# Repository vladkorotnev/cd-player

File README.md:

# ESPer CDP

## Index

* [Firmware](firm)
* [Schematics](sch)
* [Test CD](test-suite)
* [Hoard of Docs](reference)

Read the rest of the readme in the Firmware folder above...

## Rough BOM

* ESPer-CDP dev PCB for IDE bus
* ESP32-WROVER, REV3 or newer with 8MB QIO Flash and 4MB QIO PSRAM
* PCA9555D ×2
* Wolfson WM8805 (sorry, out of production, but you can still buy them here and there)
* PCM5102
* Various resistors and capacitors -- see schematic
* 12MHz XTAL
* IR Receiver and PS2 DVD remote
* ESPer-CDP Keypad PCB
* 8 12x12mm buttons
* Futaba GP1232A02 VFD display

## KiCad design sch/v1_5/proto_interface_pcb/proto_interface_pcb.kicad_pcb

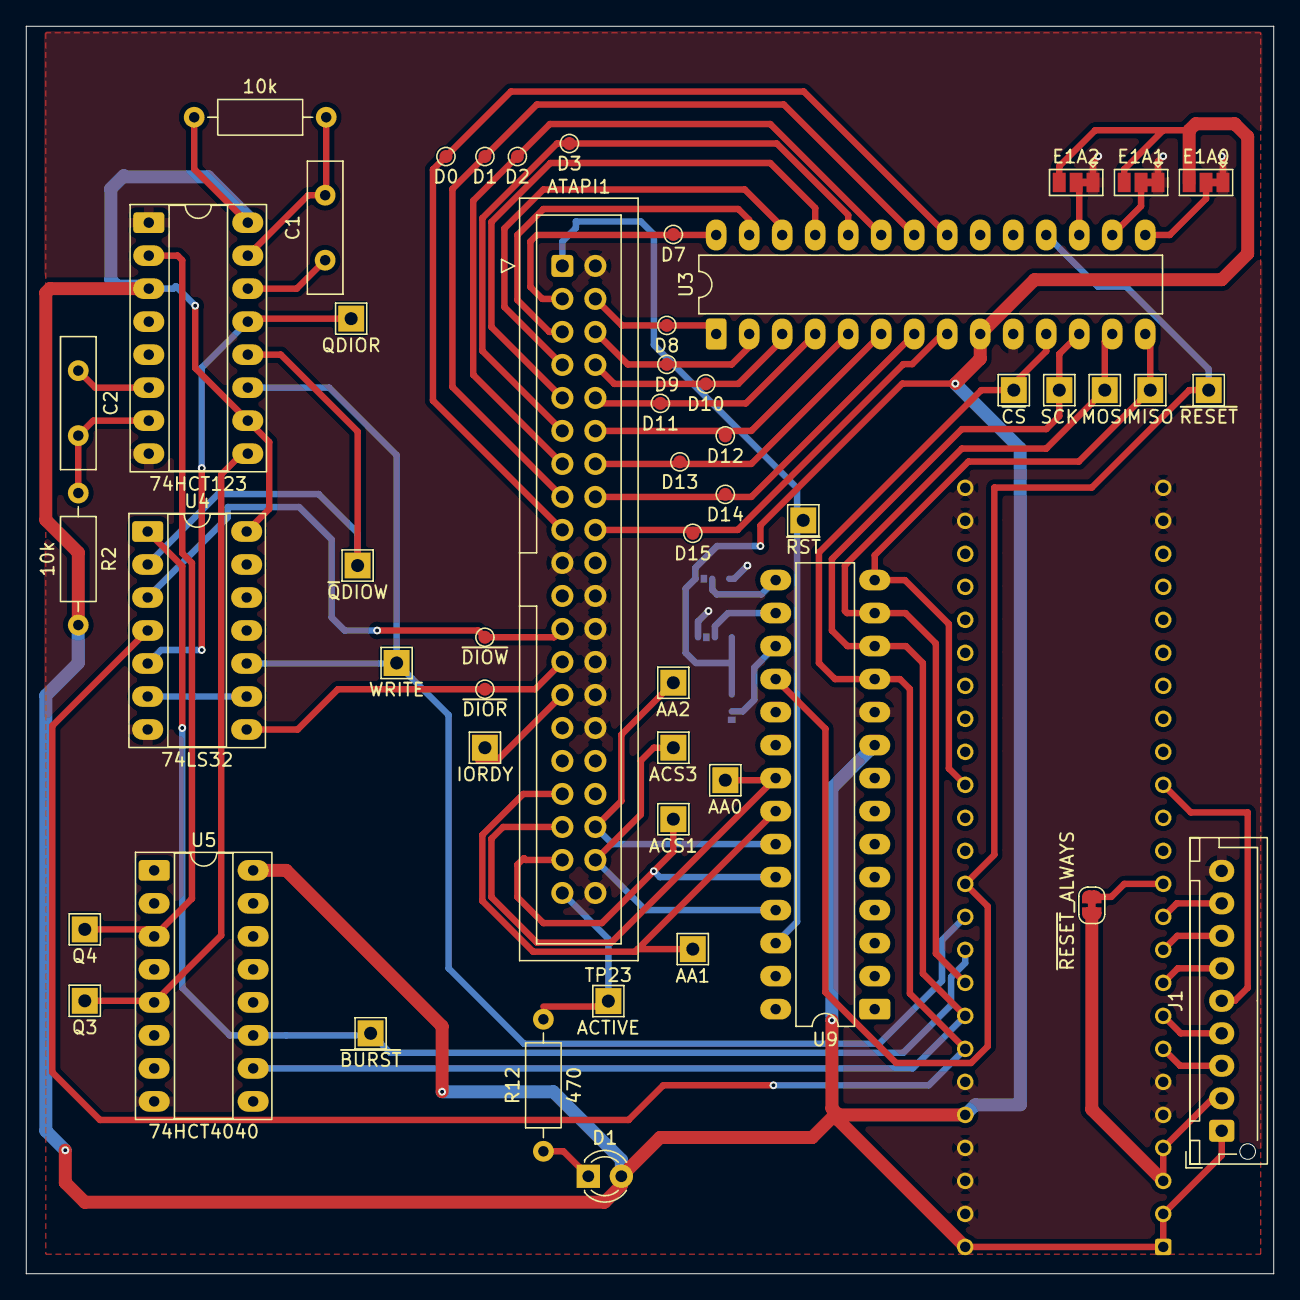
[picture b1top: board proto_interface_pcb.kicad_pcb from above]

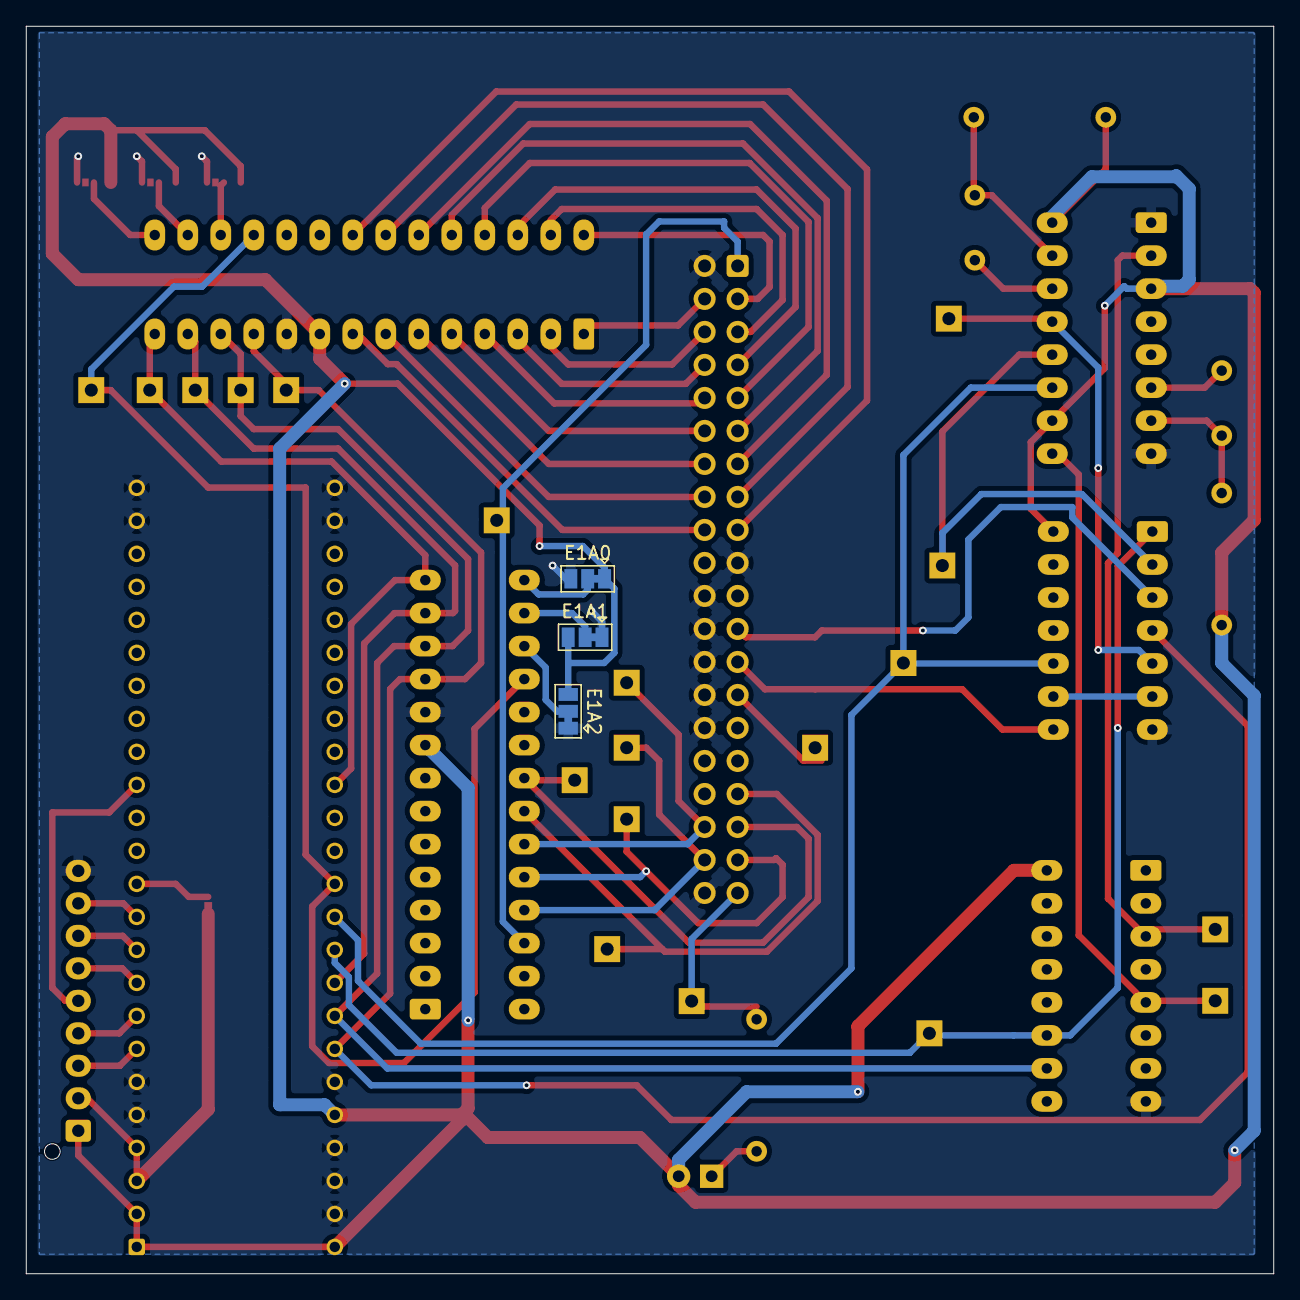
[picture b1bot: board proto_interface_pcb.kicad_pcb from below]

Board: 2 copper layers, 96.0 x 96.0 mm, 55 parts (3 on the bottom side), 59 nets.

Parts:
ATAPI1: IDC-Header_2x20_P2.54mm_Vertical
C1, C2: 220pF; C_Disc_D10.0mm_W2.5mm_P5.00mm
D1: ACTLED; LED_D3.0mm_Clear
J1: Conn_01x09_Socket; JST_XH_B9B-XH-AM_1x09_P2.50mm_Vertical
JP1, JP4: E1A0; SolderJumper-3_P1.3mm_Bridged12_Pad1.0x1.5mm
JP2, JP5: E1A1; SolderJumper-3_P1.3mm_Bridged12_Pad1.0x1.5mm
JP3, JP6: E1A2; SolderJumper-3_P1.3mm_Bridged12_Pad1.0x1.5mm
JP7: ~{RESET}_ALWAYS; SolderJumper-2_P1.3mm_Bridged_RoundedPad1.0x1.5mm
R1, R2: 10k; R_Axial_DIN0207_L6.3mm_D2.5mm_P10.16mm_Horizontal
R12: 470; R_Axial_DIN0207_L6.3mm_D2.5mm_P10.16mm_Horizontal
TP1: D0; TestPoint_Pad_D1.0mm
TP2: D1; TestPoint_Pad_D1.0mm
TP3: D2; TestPoint_Pad_D1.0mm
TP4: D3; TestPoint_Pad_D1.0mm
TP8: D7; TestPoint_Pad_D1.0mm
TP9: D8; TestPoint_Pad_D1.0mm
TP10: D9; TestPoint_Pad_D1.0mm
TP11: D10; TestPoint_Pad_D1.0mm
TP12: D11; TestPoint_Pad_D1.0mm
TP13: D12; TestPoint_Pad_D1.0mm
TP14: D13; TestPoint_Pad_D1.0mm
TP15: D14; TestPoint_Pad_D1.0mm
TP16: D15; TestPoint_Pad_D1.0mm
TP17: IORDY; TestPoint_THTPad_2.0x2.0mm_Drill1.0mm
TP18: AA0; TestPoint_THTPad_2.0x2.0mm_Drill1.0mm
TP19: AA1; TestPoint_THTPad_2.0x2.0mm_Drill1.0mm
TP20: AA2; TestPoint_THTPad_2.0x2.0mm_Drill1.0mm
TP21: ACS1; TestPoint_THTPad_2.0x2.0mm_Drill1.0mm
TP22: ACS3; TestPoint_THTPad_2.0x2.0mm_Drill1.0mm
TP23: ACTIVE; TestPoint_THTPad_2.0x2.0mm_Drill1.0mm
TP24: ~{RST}; TestPoint_THTPad_2.0x2.0mm_Drill1.0mm
TP25: ~{DIOW}; TestPoint_Pad_D1.0mm
TP26: ~{DIOR}; TestPoint_Pad_D1.0mm
TP27: ~{CS}; TestPoint_THTPad_2.0x2.0mm_Drill1.0mm
TP28: SCK; TestPoint_THTPad_2.0x2.0mm_Drill1.0mm
TP29: MOSI; TestPoint_THTPad_2.0x2.0mm_Drill1.0mm
TP30: ~{BURST}; TestPoint_THTPad_2.0x2.0mm_Drill1.0mm
TP31: WRITE; TestPoint_THTPad_2.0x2.0mm_Drill1.0mm
TP32: ~{RESET}; TestPoint_THTPad_2.0x2.0mm_Drill1.0mm
TP33: MISO; TestPoint_THTPad_2.0x2.0mm_Drill1.0mm
TP34: Q3; TestPoint_THTPad_2.0x2.0mm_Drill1.0mm
TP35: Q4; TestPoint_THTPad_2.0x2.0mm_Drill1.0mm
TP36: QDIOR; TestPoint_THTPad_2.0x2.0mm_Drill1.0mm
TP37: ~{Q}DIOW; TestPoint_THTPad_2.0x2.0mm_Drill1.0mm
U2: AE-LLCNV-LVCH16T245
U3, U9: MCP23S17x-x-SO; DIP-28_W7.62mm_LongPads
U4: 74LS32; DIP-14_W7.62mm_Socket_LongPads
U5: 74HCT4040; DIP-16_W7.62mm_Socket_LongPads
U6: 74HCT123; DIP-16_W7.62mm_Socket_LongPads

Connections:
+3V3: J1.2, JP7.2 (B), U2.3 (VB), U2.4 (VB)
+5V: D1.2 (A), J1.1, JP1.3 (B), JP2.3 (B), JP3.3 (B), JP4.1 (A), JP5.3 (B), JP6.3 (B), R1.2, R2.2, U2.1 (VA), U2.2 (VA), U2.44 (2DIR), U2.48 (VA), U3.9 (V_{DD}), U4.14 (VCC), U5.16 (VDD), U6.3 (Clr), U6.10 (B), U6.16 (VCC), U9.9 (V_{DD})
/ATAPI_MISO_5V: TP33.1 (1_1), U2.34 (2A0), U3.14 (SO), U9.14 (SO)
/ATAPI_MOSI_5V: TP29.1 (1_1), U2.40 (1A2), U3.13 (SI), U9.13 (SI)
/ATAPI_SCK_5V: TP28.1 (1_1), U2.41 (1A1), U3.12 (SCK), U5.10 (CLK), U9.12 (SCK)
/ATAPI_WRITE_5V: TP31.1 (1_1), U2.38 (1A4), U4.10, U6.11 (Clr)
/ATAPI_~RST: ATAPI1.1 (~RST), TP24.1 (1_1), U9.26 (GPA5)
/~ATAPI_BURST_5V: TP30.1 (1_1), U2.39 (1A3), U4.1, U5.11 (Reset)
/~ATAPI_CS_5V: TP27.1 (1_1), U2.42 (1A0), U3.11 (~CS), U4.4, U9.11 (~CS)
/~DIOR: ATAPI1.25 (~DIOR), TP26.1 (1_1), U4.8
/~DIOW: ATAPI1.23 (~DIOW), TP25.1 (1_1), U4.3
/~RESET_5V: TP32.1 (1_1), U2.37 (1A5), U3.18 (~RESET), U9.18 (~RESET)
ATAPI_MISO: J1.5, U2.15 (2B0)
ATAPI_MOSI: J1.6, U2.9 (1B2)
ATAPI_SCK: J1.4, U2.8 (1B1)
ATAPI_WRITE: J1.8, U2.11 (1B4)
GNDD: ATAPI1.2 (GND), ATAPI1.19 (GND), ATAPI1.22 (GND), ATAPI1.24 (GND), ATAPI1.26 (GND), ATAPI1.28 (CSEL), ATAPI1.30 (GND), ATAPI1.40 (GND), J1.9, JP1.1 (A), JP2.1 (A), JP3.1 (A), JP4.3 (B), JP5.1 (A), JP6.1 (A), U2.5 (GND), U2.6 (GND), U2.23 (GND), U2.24 (GND), U2.25 (GND), U2.26 (GND), U2.43 (GND), U2.45 (1DIR), U2.46 (2OE), U2.47 (1OE), U3.10 (V_{SS}), U4.7 (GND), U5.8 (VSS), U6.1 (A), U6.8 (GND), U9.10 (V_{SS})
unnamed: ATAPI1.35 (A0), TP18.1 (1_1), U9.21 (GPA0)
unnamed: ATAPI1.33 (A1), TP19.1 (1_1), U9.22 (GPA1)
unnamed: ATAPI1.36 (A2), TP20.1 (1_1), U9.23 (GPA2)
unnamed: ATAPI1.39 (ACTIVE), R12.2, TP23.1 (1_1)
unnamed: ATAPI1.37 (CS1), TP21.1 (1_1), U9.24 (GPA3)
unnamed: ATAPI1.38 (CS3), TP22.1 (1_1), U9.25 (GPA4)
unnamed: ATAPI1.17 (D0), TP1.1 (1_1), U3.21 (GPA0)
unnamed: ATAPI1.15 (D1), TP2.1 (1_1), U3.22 (GPA1)
unnamed: ATAPI1.13 (D2), TP3.1 (1_1), U3.23 (GPA2)
unnamed: ATAPI1.11 (D3), TP4.1 (1_1), U3.24 (GPA3)
unnamed: ATAPI1.9 (D4), U3.25 (GPA4)
unnamed: ATAPI1.7 (D5), U3.26 (GPA5)
unnamed: ATAPI1.5 (D6), U3.27 (GPA6)
unnamed: ATAPI1.3 (D7), TP8.1 (1_1), U3.28 (GPA7)
unnamed: ATAPI1.4 (D8), TP9.1 (1_1), U3.1 (GPB0)
unnamed: ATAPI1.6 (D9), TP10.1 (1_1), U3.2 (GPB1)
unnamed: ATAPI1.8 (D10), TP11.1 (1_1), U3.3 (GPB2)
unnamed: ATAPI1.10 (D11), TP12.1 (1_1), U3.4 (GPB3)
unnamed: ATAPI1.12 (D12), TP13.1 (1_1), U3.5 (GPB4)
unnamed: ATAPI1.14 (D13), TP14.1 (1_1), U3.6 (GPB5)
unnamed: ATAPI1.16 (D14), TP15.1 (1_1), U3.7 (GPB6)
unnamed: ATAPI1.18 (D15), TP16.1 (1_1), U3.8 (GPB7)
unnamed: ATAPI1.27 (IOCHRDY), TP17.1 (1_1)
unnamed: D1.1 (K), R12.1
unnamed: JP1.2 (C), U3.15 (A0)
unnamed: JP2.2 (C), U3.16 (A1)
unnamed: JP3.2 (C), U3.17 (A2)
unnamed: JP4.2 (C), U9.15 (A0)
unnamed: JP5.2 (C), U9.16 (A1)
unnamed: JP6.2 (C), U9.17 (A2)
unnamed: U4.6, U4.9
unnamed: TP34.1 (1_1), U5.5 (Q3), U6.9 (A)
unnamed: TP35.1 (1_1), U5.3 (Q4), U6.2 (B)
unnamed: C1.1, U6.14 (Cext)
unnamed: TP36.1 (1_1), U4.5, U6.13 (Q)
unnamed: C1.2, R1.1, U6.15 (RCext)
unnamed: C2.1, U6.6 (Cext)
unnamed: C2.2, R2.1, U6.7 (RCext)
unnamed: TP37.1 (1_1), U4.2, U6.12 (~Q)
~ATAPI_BURST: J1.7, U2.10 (1B3)
~ATAPI_CS: J1.3, U2.7 (1B0)
~RESET: JP7.1 (A), U2.12 (1B5)

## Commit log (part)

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2024-12-14 init
2024-12-14 schematic wip
2025-01-16 IN12 Nixie Display Module
2025-01-16 wip (use RS232 for the display in the end)
2025-01-17 [wip] all PCBs pass connectivity tests and DRC
2025-01-21 wip jlc order
2025-01-23 Create test suite files
2025-01-27 Errata of received PCBs, Nixierator rev2
2025-01-27 i2c expander address correction
2025-01-28 even more errata
2025-01-28 Create barebones firmware
2025-01-28 This seems to communicate with the drive just fine!
2025-01-29 It ejects!
2025-01-29 fix endianness bug; changer control seems to work
2025-02-01 ok this kinda works in many ways
2025-02-01 some metadata arch
2025-02-01 Musicbrainz client
2025-02-01 CD-Enhanced quirk for old drives
2025-02-02 take out the trash
2025-02-02 better ready handling; CD-TEXT seems to read
2025-02-02 Tentative WM8805 driver for when it arrives finally
2025-02-03 Somewhat of a working player model? (this REALLY needs size optimizations now!)
2025-02-03 Small touches before I go sleep
2025-02-04 missing stop condition
2025-02-04 Why not also show lyrics
2025-02-05 working spdif and dac!
2025-02-05 add ntp, start implementing changer
2025-02-11 display test
2025-02-12 begin implementing display library
2025-02-13 ok this seems to be able to draw even outside of byte boundaries
2025-02-13 boot screen PoC/mockup
2025-02-14 copy font stuff from PIS-OS; vertical pixel buffer rendering
2025-02-14 Fonts kinda work
2025-02-15 Fix need_layout, fix negative X coord blitting
2025-02-15 don't code after a work day kids (also yay jumping mek)
2025-02-15 start building up arch of various modes
2025-02-16 Fonts n things, audio routing class
2025-02-16 POC taking shape huh?
2025-02-18 Fed up with the signed unsigned conversion
2025-02-18 Lyrics display works but no word wrap; fix not byte-aligned blitting; add k8x12 font
2025-02-19 working caching and small fixes here and there
2025-02-19 smooth scroll, overall more responsive, and shut up a warning
2025-02-20 statusbar design tweaks; word wrap and center justify lyrics
2025-02-20 center title when no artist name
2025-02-21 doc updates, fixes of UI stuff, shuffle mode, WiFi service module
2025-02-21 Move player to correct folder
2025-02-21 data track related polish
2025-02-22 experiments with data cd
2025-02-22 bump i2c freq and readme, fix layout bug when shuffle
2025-02-23 this seems to read a sector off the CD-R
2025-02-24 kinda works but crashes in realloc when read_direntry
2025-02-24 begin radio streaming work
2025-02-25 radio now playing
2025-02-25 not using AudioPlayer class now
2025-02-25 somewhat synced labels
2025-02-26 laggy but async playing, relax-fm also not buggy
2025-02-26 well, kind of?
2025-02-27 mostly working radio receiver
2025-02-27 probably ok for the time being
2025-02-27 Fix cddb ll definition conflict with ESP32 bt stack
2025-02-27 Add bluetooth receiver mode
2025-02-28 seems to be more stable radio pipeline; finish up bt mode
2025-02-28 even more stable? (see memo!! todo make patcher)
2025-03-01 somewhat works, time to move on ffs
2025-03-01 mode switching
2025-03-01 snapshot before i try to migrate this thing to IDF
2025-03-01 Well, it builds with all modes in the firmware now...
2025-03-02 set specific esp_littlefs commit/version
2025-03-02 Exit out of BT mode correctly
2025-03-02 Test a few more drives
2025-03-02 If you are missing a delete(), then someone else definitely has one extra!
2025-03-02 Mostly works, let's continyue trying with IDF then
2025-03-02 eliminate scroll madness in cd mode
2025-03-03 Remote control support; minor fixes; no crashes when switching net radio stations
2025-03-03 Prefs framework and kind of a boot screen
2025-03-04 optimize WiFi icon redrawing
2025-03-04 Add a boot screen and standby mode (actual power consumption TBD)
2025-03-04 begin making menu system
2025-03-05 volume bar in bt mode; scroll bar in list view
2025-03-05 Well, it's not clean but it navigates so there's that
2025-03-05 Syntax sugar-ish
2025-03-06 Text input in menu and all that
2025-03-06 add QQ music lyric source
2025-03-06 Multi language support
2025-03-07 Menus n locales n shit
2025-03-07 LastFM scrobbling
2025-03-07 Make threaded scrobbler actually do its job
2025-03-07 At this point I kinda wish I was writing in C
2025-03-08 All this pain to optimize some stack sizes
2025-03-08 Hopefully go around the bug when updating label from no scroll to scroll results in it being stuck off screen
2025-03-09 somewhat working station url editor
2025-03-10 Lock the tray when in standby
2025-03-10 OTA flashing
2025-03-10 Netease lyric source
2025-03-11 Fix language menu
2025-03-13 HU, DE, BL locales
2025-03-13 License-ish thing
2025-03-14 Schematic pdfs (#2)
2025-03-17 Support media/aacp content-type
2025-03-18 Try create CI
2025-03-18 Let's see if CI build cache worked...
2025-03-18 Introduce lastfm secrets into CI
2025-03-18 Add HTTP FVU functionality
2025-03-18 Fix CI branch name
2025-03-18 ci: Publish firmwares at 802b9d7
2025-03-18 Automated publish
2025-03-18 This commit will be automatically published
2025-03-20 Add passthrough relay on pin 19
2025-03-21 Allow recovering out of some less fatal conditions via OTA without opening the case
2025-03-21 digit key on remote now plays the track by the number
2025-03-26 ci: Publish firmwares at 5c64a6b
2025-03-26 ci: Publish firmwares at 2b486a9
2025-03-26 enable OTAFVU in CI
2025-03-26 Fix unpausing after FF/REW getting the thing stuck in FF/REW
2025-03-26 Support entering track number from remote
2025-03-26 Bump version to 1.2
2025-03-26 ci: Publish firmwares at 538700e
2025-03-26 Don't explode in OTAFVU startup if WiFi settings are lost for some reason
2025-03-26 ci: Publish firmwares at d700487
2025-03-26 Fix entering shuffle during playback not actually starting shuffle
2025-03-27 unbreak bt receiver
2025-03-27 Fix draw_rect and add frame around lyrics
2025-03-27 Sneaky version bump
2025-03-27 Hopefully some improvement to performance by using a static buffer for the compositing
2025-03-27 ci: Publish firmwares at 358c034
2025-03-29 Support LITE-ON LTR-48246S
2025-03-29 Support LITE-ON (JLMS) XJ-HD166S
2025-03-29 Fun with mode sense and select
2025-03-29 Fix quirk detection typos
2025-03-30 CD drive diagnostic view
2025-03-30 Fix capability packet definition, show fvu flavor in about
2025-03-30 ci: Publish firmwares at 2425e1b
2025-04-02 Make some drives (looking at you LiteOn) less obnoxiously loud
2025-04-02 ci: Publish firmwares at f1c82e4
2025-04-06 Add LITE ON LTN-486, TEAC DV-W516GDM
2025-04-06 ci: Publish firmwares at dbd8f9c
2025-04-24 Test BENQ DW1620
2025-04-24 Add default radio stations
2025-04-24 Don't leave lyrics hanging for a while if current track had a last line but the next track has none
2025-04-24 Version bump
2025-04-24 ci: Publish firmwares at f5774dc
2025-04-24 Cancel CI on push new commit
2025-04-27 work around the crash when querying CD meta without wifi connected
2025-04-28 Support ASUS CD-S520B
2025-04-28 ci: Publish firmwares at 3488a73
2025-05-29 Add Telnet logging
2025-05-29 Somewhat ass but kinda working workaround for settings menu stack overflow...
2025-05-30 Improve netradio performance by removing PCM task
2025-05-30 Minor version bump
2025-05-30 ci: Publish firmwares at 7d443fa
2025-06-01 Fix radio crash regression in 1.2.4
2025-06-01 ci: Publish firmwares at 3051935
2025-06-01 This core allocation seems to have better radio stability?
2025-06-02 More messing about with the radio and debug view
2025-06-02 Show version number on boot screen
2025-06-03 Remove unusable FTP item from source list
2025-06-03 Rudimentary FTP folder browsing
2025-06-03 Crashes often but kinda plays?
2025-06-10 ci: Publish firmwares at bc032fb
2025-10-07 More ftp wip
2025-10-07 Changer related changes
2026-06-06 bump version
2026-06-06 fix stupid typos in cdtext
2026-06-07 allow disable cd text
2026-06-07 fix malformed cdtext parsing edgecase (closes #7)
2026-06-07 ci: Publish firmwares at 90a6c66
2026-06-08 add redundancy to cdtext by checking CRC
2026-06-08 ci: Publish firmwares at da41650
